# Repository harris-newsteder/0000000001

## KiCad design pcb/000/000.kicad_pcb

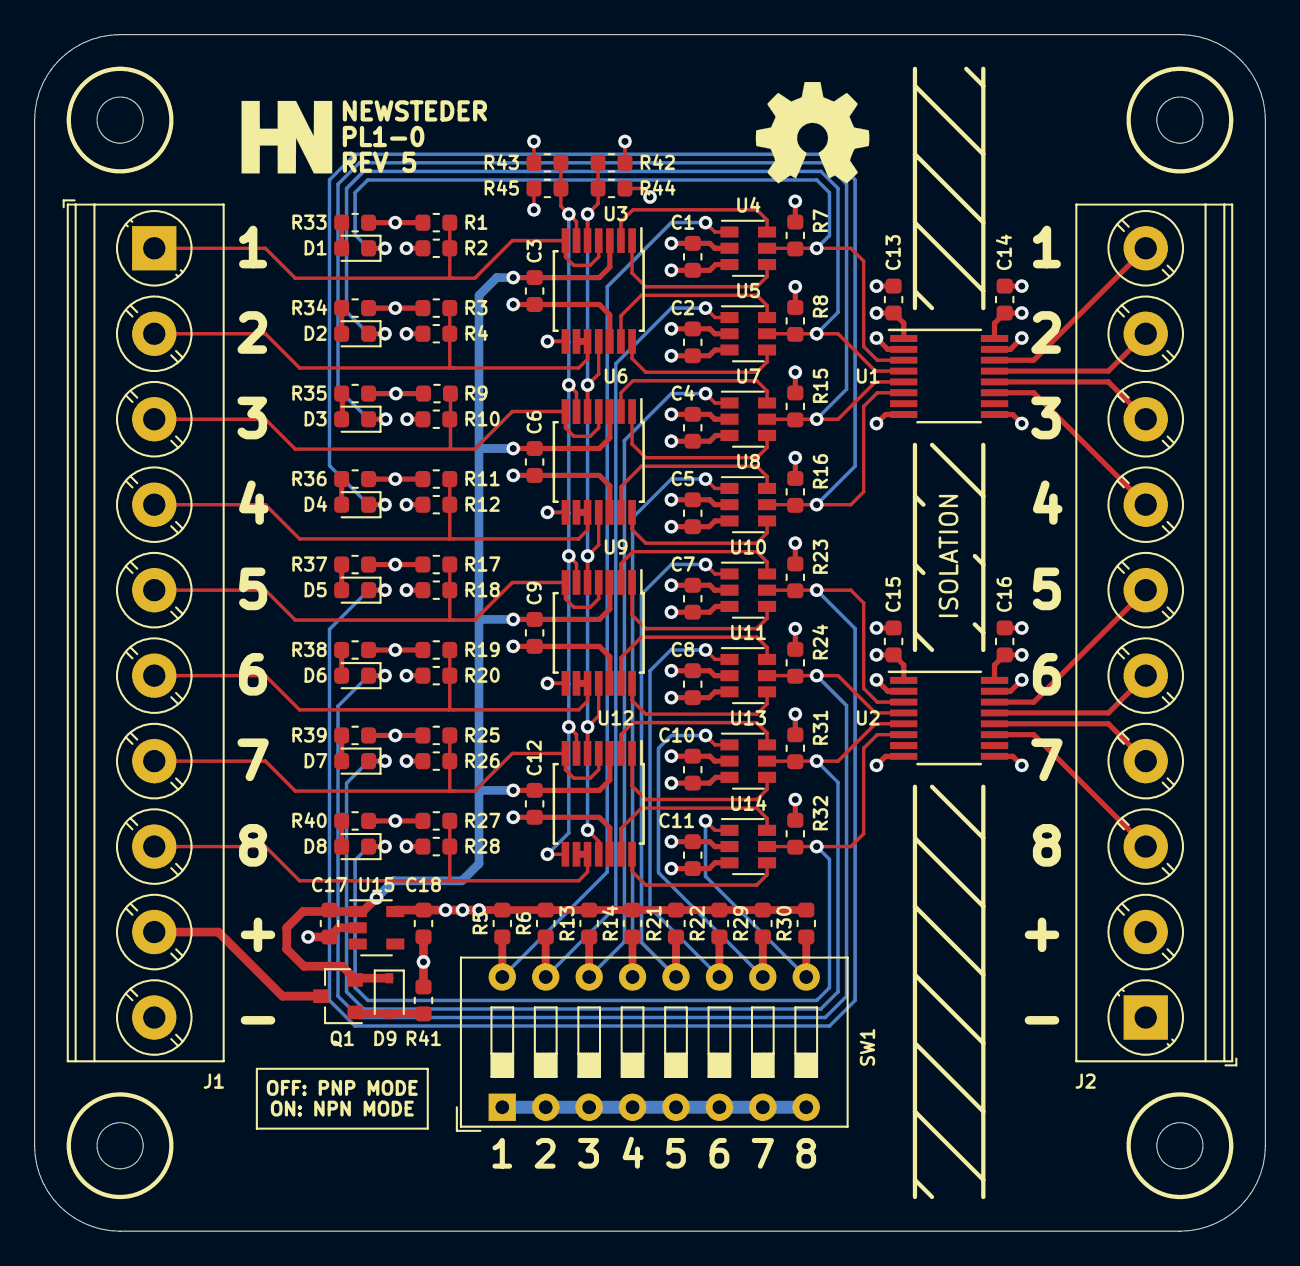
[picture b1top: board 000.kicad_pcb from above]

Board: 4 copper layers, 72.0 x 70.0 mm, 91 parts (0 on the bottom side), 65 nets.

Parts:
C1, C2, C3, C4, C5, C6, C7, C8, C9, C10, C11, C12: 0.1uF; C_0603_1608Metric
C13, C14, C15, C16: C; C_0603_1608Metric
C17: 1.0uF; C_0603_1608Metric
C18: 1.5uF; C_0603_1608Metric
D1, D2, D3, D4, D5, D6, D7, D8: LED; LED_0603_1608Metric
D9: MM3Z10VT1G; D_SOD-323
J1: INPUT TERMINAL; TerminalBlock_Phoenix_PT-1,5-10-5.0-H_1x10_P5.00mm_Horizont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
J2: OUTPUT TERMINAL; TerminalBlock_Phoenix_PT-1,5-10-5.0-H_1x10_P5.00mm_Horizont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
Q1: ZXMP10A13FTA; SOT-23
R1, R2, R3, R4, R5, R6, R7, R8, R9, R10, R11, R12, R13, R14, R15, R16, R17, R18, R19, R20, R21, R22, R23, R24, R25, R26, R27, R28, R29, R30, R31, R32, R43, R44: 10kOhm; R_0603_1608Metric
R33, R34, R35, R36, R37, R38, R39, R40: 1kOhm; R_0603_1608Metric
R41: 100kOhm; R_0603_1608Metric
R42, R45: 6.65kOhm; R_0603_1608Metric
SW1: MODE SELECT SWITCH; SW_DIP_SPSTx08_Slide_9.78x22.5mm_W7.62mm_P2.54mm
U1, U2: Si8645BA-B-IU; QSOP-16_3.9x4.9mm_P0.635mm
U3, U6, U9, U12: LM339; TSSOP-14_4.4x5mm_P0.65mm
U4, U5, U7, U8, U10, U11, U13, U14: STG719STR; SOT-23-6
U15: TPS70950DBVR; SOT-23-5

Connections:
2.0V: R43.2, R45.1, U3.6, U3.8, U6.6, U6.8, U9.6, U9.8, U12.6, U12.8
3.0V: R42.2, R44.1, U3.5, U3.11, U6.5, U6.11, U9.5, U9.11, U12.5, U12.11
+5V: C1.1, C2.1, C4.1, C5.1, C7.1, C8.1, C10.1, C11.1, C13.2, C15.2, C18.1, R1.1, R3.1, R5.1, R6.1, R7.1, R8.1, R9.1, R11.1, R13.1, R14.1, R15.1, R16.1, R17.1, R19.1, R21.1, R22.1, R23.1, R24.1, R25.1, R27.1, R29.1, R30.1, R31.1, R32.1, R33.1, R34.1, R35.1, R36.1, R37.1, R38.1, R39.1, R40.1, R42.1, R43.1, U1.1, U2.1, U4.2, U5.2, U7.2, U8.2, U10.2, U11.2, U13.2, U14.2, U15.5
+VDC: C3.1, C6.1, C9.1, C12.1, C17.1, D9.1, Q1.2, U3.3, U6.3, U9.3, U12.3, U15.1
/OUT_0: J2.10, U1.14
/OUT_1: J2.9, U1.13
/OUT_2: J2.8, U1.12
/OUT_3: J2.7, U1.11
/OUT_4: J2.6, U2.14
/OUT_5: J2.5, U2.13
/OUT_6: J2.4, U2.12
/OUT_7: J2.3, U2.11
/SIG_0: J1.1, R1.2, R2.1, U3.4, U3.7
/SIG_1: J1.2, R3.2, R4.1, U3.9, U3.10
/SIG_2: J1.3, R9.2, R10.1, U6.4, U6.7
/SIG_3: J1.4, R11.2, R12.1, U6.9, U6.10
/SIG_4: J1.5, R17.2, R18.1, U9.4, U9.7
/SIG_5: J1.6, R19.2, R20.1, U9.9, U9.10
/SIG_6: J1.7, R25.2, R26.1, U12.4, U12.7
/SIG_7: J1.8, R27.2, R28.1, U12.9, U12.10
/UOUT_0: D1.1, R7.2, U1.3, U4.5
/UOUT_1: D2.1, R8.2, U1.4, U5.5
/UOUT_2: D3.1, R15.2, U1.5, U7.5
/UOUT_3: D4.1, R16.2, U1.6, U8.5
/UOUT_5: D5.1, R23.2, U2.3, U10.5
/UOUT_6: D6.1, R24.2, U2.4, U11.5
/UOUT_7: D7.1, R31.2, U2.5, U13.5
/UOUT_8: D8.1, R32.2, U2.6, U14.5
GND: C1.2, C2.2, C3.2, C4.2, C5.2, C6.2, C7.2, C8.2, C9.2, C10.2, C11.2, C12.2, C13.1, C15.1, C17.2, C18.2, J1.10, R2.2, R4.2, R10.2, R12.2, R18.2, R20.2, R26.2, R28.2, R41.2, R44.2, R45.2, SW1.1, SW1.2, SW1.3, SW1.4, SW1.5, SW1.6, SW1.7, SW1.8, U1.2, U1.8, U2.2, U2.8, U3.12, U4.3, U5.3, U6.12, U7.3, U8.3, U9.12, U10.3, U11.3, U12.12, U13.3, U14.3, U15.2
LV+: C14.2, C16.2, J2.2, U1.16, U2.16
LV-: C14.1, C16.1, J2.1, U1.9, U1.15, U2.9, U2.15
MODE_0: R5.2, SW1.16, U4.1
MODE_1: R6.2, SW1.15, U5.1
MODE_2: R13.2, SW1.14, U7.1
MODE_3: R14.2, SW1.13, U8.1
MODE_4: R21.2, SW1.12, U10.1
MODE_5: R22.2, SW1.11, U11.1
MODE_6: R29.2, SW1.10, U13.1
MODE_7: R30.2, SW1.9, U14.1
unnamed: D1.2, R33.2
unnamed: D2.2, R34.2
unnamed: D3.2, R35.2
unnamed: D4.2, R36.2
unnamed: D5.2, R37.2
unnamed: D6.2, R38.2
unnamed: D7.2, R39.2
unnamed: D8.2, R40.2
unnamed: D9.2, Q1.1, R41.1
unnamed: U3.1, U4.4
unnamed: U3.2, U4.6
unnamed: U3.13, U5.6
unnamed: U3.14, U5.4
unnamed: U6.1, U7.4
unnamed: U6.2, U7.6
unnamed: U6.13, U8.6
unnamed: U6.14, U8.4
unnamed: U9.1, U10.4
unnamed: U9.2, U10.6
unnamed: U9.14, U11.4
unnamed: U9.13, U11.6
unnamed: U12.1, U13.4
unnamed: U12.2, U13.6
unnamed: U12.13, U14.6
unnamed: U12.14, U14.4
VIN: J1.9, Q1.3

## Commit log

2019-12-22 rev 4 commit, works but uses a lot of power. commiting this change before going over to the new design
2020-01-20 REV 5 of the board, much better power consumption and reponse time but the LDO is no good, only barely works and when you hook up an ammeter it blows the fuck up
